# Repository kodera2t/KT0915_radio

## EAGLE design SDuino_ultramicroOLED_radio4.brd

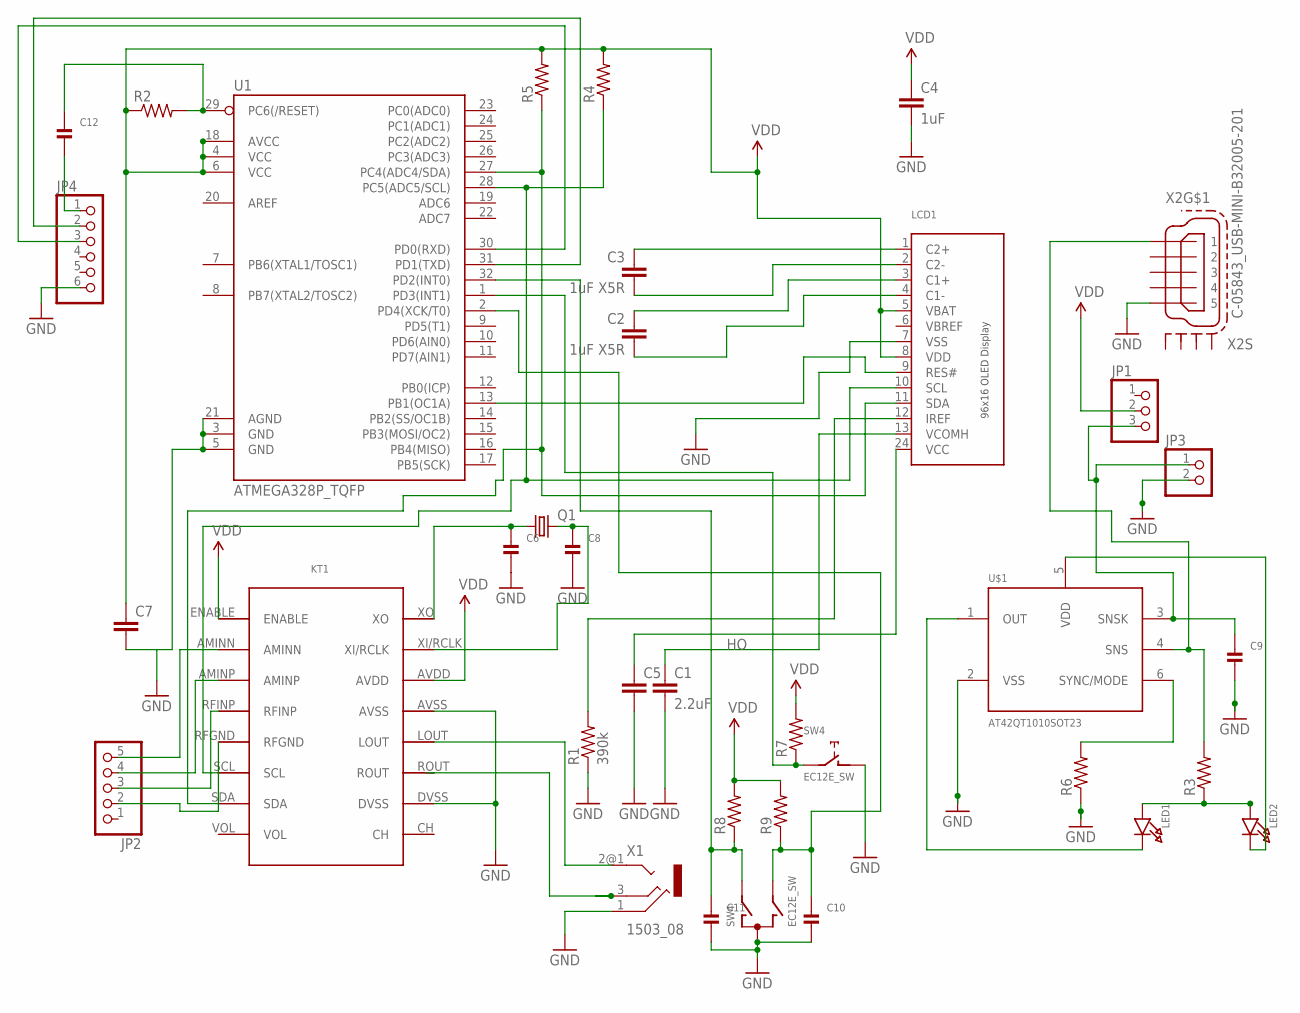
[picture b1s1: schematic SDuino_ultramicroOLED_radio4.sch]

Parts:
C1: 2.2uF; 0805
C2, C3: 1uF X5R; 0805
C4: 1uF; 0603-CAP
C5, C7: CC0603; C0603
C6, C8, C9, C10, C11, C12: CAP_CERAMIC0603; 0603
JP1: HEADER-1X3; 1X03_OVAL
JP2: HEADER-1X5; 1X05_OVAL
JP3: HEADER-1X2; 1X02_OVAL
JP4: HEADER-1X6; 1X06_OVAL
KT1: KT0915
LCD1: DISP_OLED_UG-9616GLBBG02; UG-9616GLBBG02_0.65MM_WRAPAROUND
LED1, LED2: LED0603; CHIPLED_0603
Q1: CRYSTALTC26V; TC26V
R1: 390k; 0603-RES
R2, R3, R4, R5, R6, R7, R8, R9: R-US_R0603; R0603
SW4: EC12E_SW; ALPS_EC12E_SW
U1: ATMEGA328P_TQFP; TQFP32-08
U$1: AT42QT1010SOT23; SOT23-6
X1: 1503_08
X2: C-05843_USB-MINI-B32005-201; 32005-201

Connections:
C1N: C2.2, LCD1.4 (C1-)
C1P: C2.1, LCD1.3 (C1+)
C2N: C3.2, LCD1.2 (C2-)
C2P: C3.1, LCD1.1 (C2+)
GND: C1.2, C4.2, C5.2, C6.2, C7.2, C8.2, C9.2, C10.2, C11.2, JP3.2, JP4.6, KT1.AVSS, KT1.DVSS, LCD1.7 (VSS), R1.1, R6.1, SW4.C, SW4.D (1), U1.3 (GND), U1.5 (GND), U1.21 (AGND), U$1.2 (VSS), X1.1, X2.5
HO: C1.1, LCD1.13 (VCOMH)
IREF: LCD1.12 (IREF), R1.2
unnamed: KT1.LOUT, X1.2@1 (2)
unnamed: C12.1, R2.2, U1.29 (PC6(/RESET))
unnamed: LCD1.9 (RES#), U1.13 (PB1(OC1A))
unnamed: C6.1, KT1.XO, Q1.1
unnamed: C8.1, KT1.XI/RCLK, Q1.2
unnamed: KT1.SCL, LCD1.10 (SCL), R4.1, U1.28 (PC5(ADC5/SCL))
unnamed: KT1.ROUT, X1.3
unnamed: R3.2, U$1.4 (SNS), X2.1
unnamed: JP2.5, KT1.AMINN
unnamed: KT1.SDA, LCD1.11 (SDA), R5.1, U1.27 (PC4(ADC4/SDA))
unnamed: JP2.4, KT1.AMINP
unnamed: JP2.3, KT1.RFINP
unnamed: JP2.2, KT1.RFGND
unnamed: JP4.3, U1.30 (PD0(RXD))
unnamed: C11.1, R8.1, SW4.A, U1.32 (PD2(INT0))
unnamed: C10.1, R9.1, SW4.B, U1.2 (PD4(XCK/T0))
unnamed: LED1.A, LED2.A, R3.1
unnamed: LED1.C, U$1.1 (OUT)
unnamed: LED2.C, U$1.5 (VDD)
unnamed: C9.1, JP1.3, JP3.1, U$1.3 (SNSK)
unnamed: R7.1, SW4.E (2), U1.1 (PD3(INT1))
unnamed: R6.2, U$1.6 (SYNC/MODE)
unnamed: C12.2, JP4.1
unnamed: JP4.2, U1.31 (PD1(TXD))
VCOMH: C5.1, LCD1.24 (VCC)
VDD: C4.1, C7.1, JP1.2, KT1.AVDD, KT1.ENABLE, LCD1.5 (VBAT), LCD1.8 (VDD), R2.1, R4.2, R5.2, R7.2, R8.2, R9.2, U1.4 (VCC), U1.6 (VCC), U1.18 (AVCC)

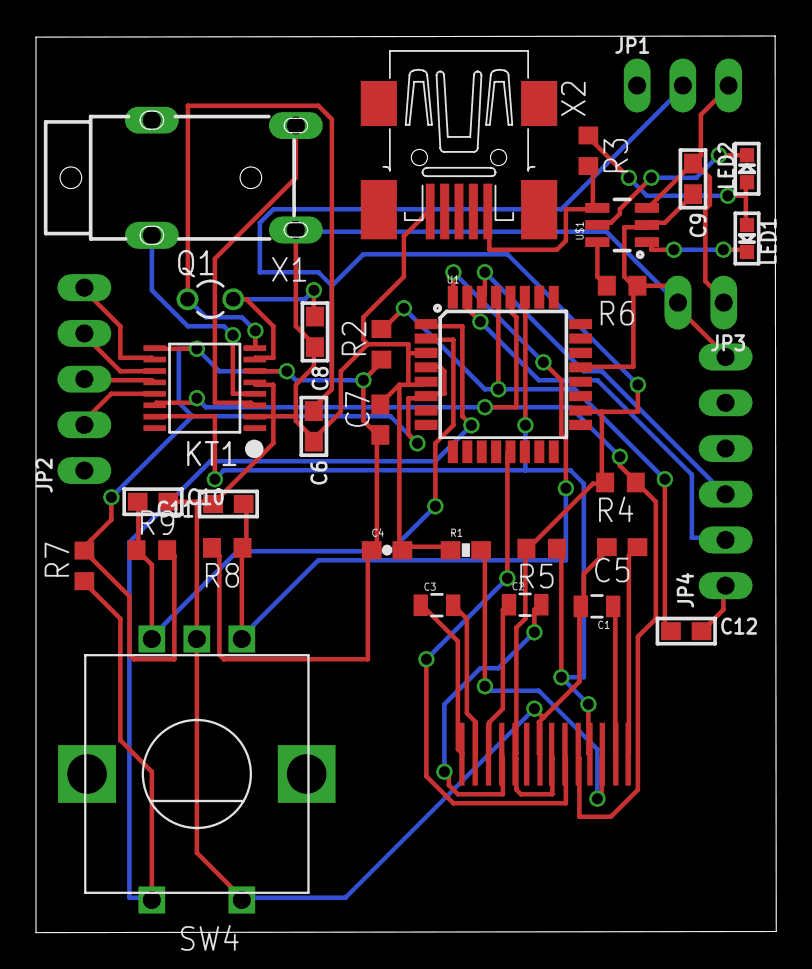
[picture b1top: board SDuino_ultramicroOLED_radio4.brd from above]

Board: 2 copper layers, 41.1 x 49.8 mm, 35 parts (1 on the bottom side), 33 nets.

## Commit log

2016-08-01 initial submission
2016-08-04 Improved firmware for better AM reception
2016-08-14 file for radio
2016-08-14 firmwares
2016-09-01 library which I used for ultra
2016-09-07 Digital audio level control with RSSI graphical bar indicator

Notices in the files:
parts and their libraries:
SparkFun-Passives: Licensing: Creative Commons ShareAlike 4.0 International - https://creativecommons.org/licenses/by-sa/4.0
OLED_mod: This work is placed in the public domain, and may be freely used for commercial and non-commercial work with the following conditions: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
